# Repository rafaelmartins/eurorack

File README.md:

# eurorack

Designing and building an Eurorack synthesizer at home.

## General terms

- Everything other than the case and power supply should be designed from scratch, at home.
- PCBs are designed to be easily assembled at home.
- PTH is preferred, but SMD parts are allowed.
- Bare MCUs are preferred, but custom PCB-friendly development boards (like Raspberry Pi Pico) are allowed when the bare MCU is not easy to hand solder.

## License

Unless otherwise noted, these are the applicable licenses:

- Source code: [BSD 3-Clause "New" or "Revised" License](https://spdx.org/licenses/BSD-3-Clause.html)
- Hardware design (including 3d models, schematics, PCBs, etc): [CERN Open Hardware Licence Version 2 - Strongly Reciprocal](https://spdx.org/licenses/CERN-OHL-S-2.0.html)

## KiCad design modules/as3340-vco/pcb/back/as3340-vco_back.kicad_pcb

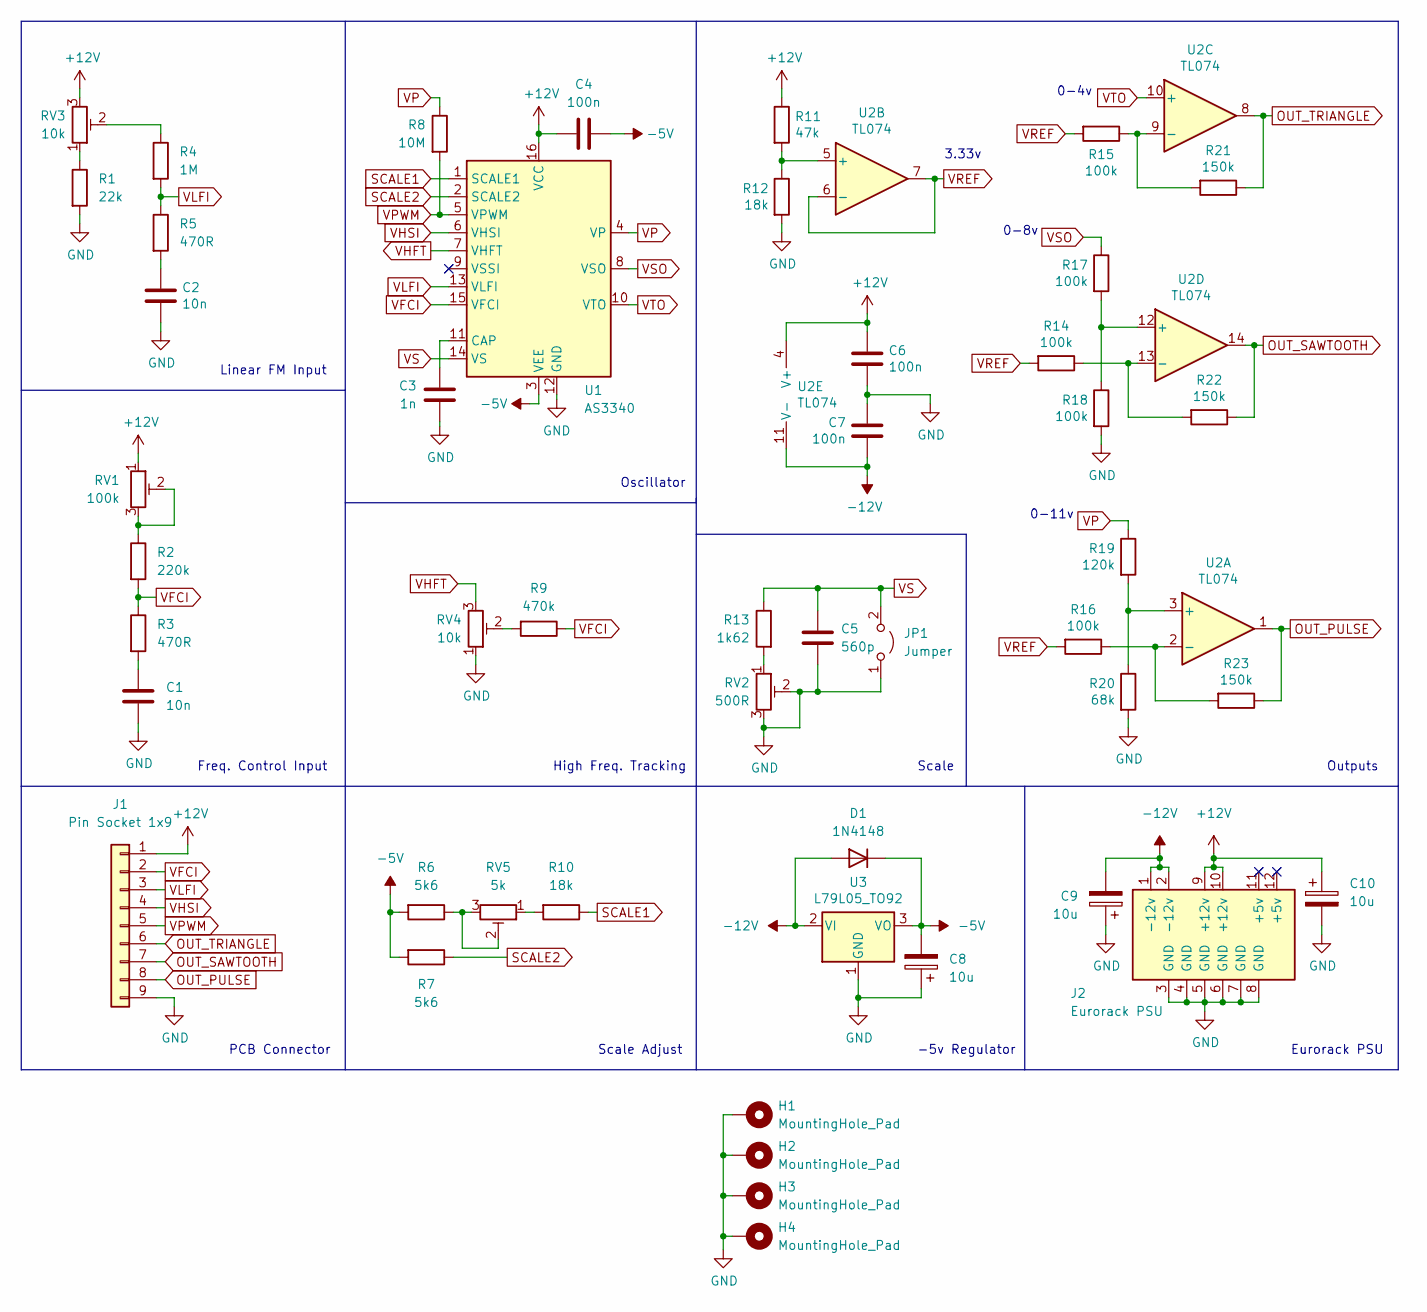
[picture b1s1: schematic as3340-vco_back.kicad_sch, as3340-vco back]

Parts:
C1, C2: 10n; C_Disc_D3.0mm_W1.6mm_P2.50mm
C3: 1n; C_Rect_L7.2mm_W3.0mm_P5.00mm_FKS2_FKP2_MKS2_MKP2
C4, C6, C7: 100n; C_Disc_D4.7mm_W2.5mm_P5.00mm
C5: 560p; C_Disc_D3.0mm_W1.6mm_P2.50mm
C8, C9, C10: 10u; CP_Radial_D5.0mm_P2.50mm
D1: 1N4148; D_DO-35_SOD27_P7.62mm_Horizontal
H1, H2, H3, H4: MountingHole_Pad; MountingHole_2.2mm_M2_Pad_Via
J1: Pin Socket 1x9; PinSocket_1x09_P2.54mm_Vertical
J2: Eurorack PSU; IDC-Header_2x08_P2.54mm_Vertical
JP1: Jumper; PinHeader_1x02_P2.54mm_Vertical
R1: 22k; R_Axial_DIN0207_L6.3mm_D2.5mm_P10.16mm_Horizontal
R2: 220k; R_Axial_DIN0207_L6.3mm_D2.5mm_P10.16mm_Horizontal
R3, R5: 470R; R_Axial_DIN0207_L6.3mm_D2.5mm_P10.16mm_Horizontal
R4: 1M; R_Axial_DIN0207_L6.3mm_D2.5mm_P10.16mm_Horizontal
R6, R7: 5k6; R_Axial_DIN0207_L6.3mm_D2.5mm_P10.16mm_Horizontal
R8: 10M; R_Axial_DIN0207_L6.3mm_D2.5mm_P10.16mm_Horizontal
R9: 470k; R_Axial_DIN0207_L6.3mm_D2.5mm_P10.16mm_Horizontal
R10, R12: 18k; R_Axial_DIN0207_L6.3mm_D2.5mm_P10.16mm_Horizontal
R11: 47k; R_Axial_DIN0207_L6.3mm_D2.5mm_P10.16mm_Horizontal
R13: 1k62; R_Axial_DIN0207_L6.3mm_D2.5mm_P10.16mm_Horizontal
R14, R15, R16, R17, R18: 100k; R_Axial_DIN0207_L6.3mm_D2.5mm_P10.16mm_Horizontal
R19: 120k; R_Axial_DIN0207_L6.3mm_D2.5mm_P10.16mm_Horizontal
R20: 68k; R_Axial_DIN0207_L6.3mm_D2.5mm_P10.16mm_Horizontal
R21, R22, R23: 150k; R_Axial_DIN0207_L6.3mm_D2.5mm_P10.16mm_Horizontal
RV1: 100k; Potentiometer_Vishay_M64Y_Horizontal
RV2: 500R; Potentiometer_Vishay_M64Y_Horizontal
RV3, RV4: 10k; Potentiometer_Vishay_M64Y_Horizontal
RV5: 5k; Potentiometer_Vishay_M64Y_Horizontal
U1: AS3340; DIP-16_W7.62mm
U2: TL074; DIP-14_W7.62mm
U3: L79L05_TO92; TO-92_Wide

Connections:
+12V: C4.1, C6.1, C10.1, J1.1, J2.9 (+12v), J2.10 (+12v), R11.1, RV1.1, RV3.3, U1.16 (VCC), U2.4 (V+)
-5V: C4.2, C8.2, D1.1 (K), R6.2, R7.2, U1.3 (VEE), U3.3 (VO)
-12V: C7.2, C9.2, D1.2 (A), J2.1 (-12v), J2.2 (-12v), U2.11 (V-), U3.2 (VI)
GND: C1.2, C2.2, C3.2, C5.2, C6.2, C7.1, C8.1, C9.1, C10.2, H1.1, H2.1, H3.1, H4.1, J1.9, J2.3 (GND), J2.4 (GND), J2.5 (GND), J2.6 (GND), J2.7 (GND), J2.8 (GND), JP1.1 (A), R1.2, R12.2, R18.2, R20.2, RV2.2, RV2.3, RV4.1, U1.12 (GND), U3.1 (GND)
unnamed: C1.1, R3.2
unnamed: C2.1, R5.2
unnamed: C3.1, U1.11 (CAP)
unnamed: R1.1, RV3.1
unnamed: R2.1, RV1.2, RV1.3
unnamed: R4.1, RV3.2
unnamed: R6.1, RV5.2, RV5.3
unnamed: R9.2, RV4.2
unnamed: R10.2, RV5.1
unnamed: R11.2, R12.1, U2.5 (+)
unnamed: R13.2, RV2.1
unnamed: R14.1, R22.2, U2.13 (-)
unnamed: R15.1, R21.2, U2.9 (-)
unnamed: R16.1, R23.2, U2.2 (-)
unnamed: R17.2, R18.1, U2.12 (+)
unnamed: R19.2, R20.1, U2.3 (+)
OUT_PULSE: J1.8, R23.1, U2.1
OUT_SAWTOOTH: J1.7, R22.1, U2.14
OUT_TRIANGLE: J1.6, R21.1, U2.8
SCALE1: R10.1, U1.1 (SCALE1)
SCALE2: R7.1, U1.2 (SCALE2)
VFCI: J1.2, R2.2, R3.1, R9.1, U1.15 (VFCI)
VHFT: RV4.3, U1.7 (VHFT)
VHSI: J1.4, U1.6 (VHSI)
VLFI: J1.3, R4.2, R5.1, U1.13 (VLFI)
VP: R8.1, R19.1, U1.4 (VP)
VPWM: J1.5, R8.2, U1.5 (VPWM)
VREF: R14.2, R15.2, R16.2, U2.6 (-), U2.7
VS: C5.1, JP1.2 (B), R13.1, U1.14 (VS)
VSO: R17.1, U1.8 (VSO)
VTO: U1.10 (VTO), U2.10 (+)

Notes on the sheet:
PCB Connector
Oscillator
-5v Regulator
Linear FM Input
Freq. Control Input
High Freq. Tracking
0-4v
Outputs
3.33v
0-8v
Eurorack PSU
Scale Adjust
0-11v
Scale

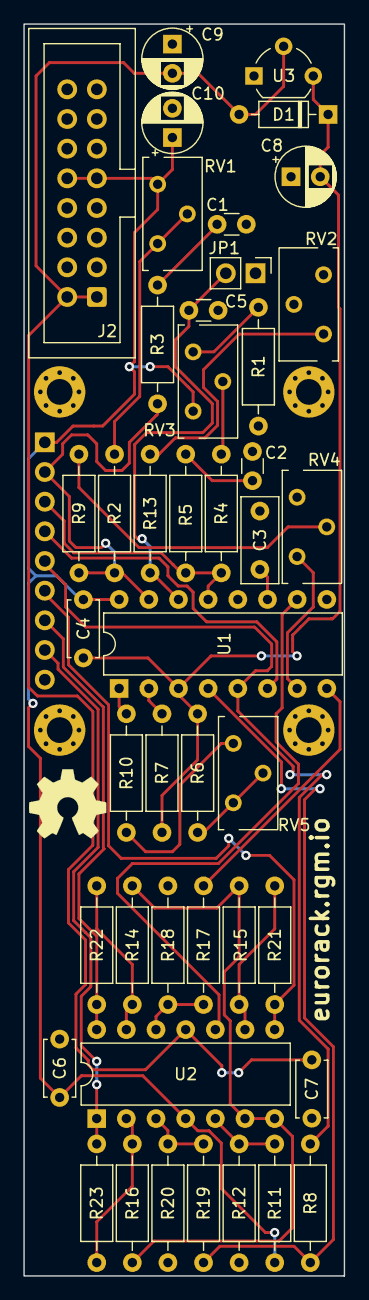
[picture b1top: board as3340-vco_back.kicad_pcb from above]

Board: 2 copper layers, 27.4 x 107.2 mm, 49 parts (1 on the bottom side), 35 nets.

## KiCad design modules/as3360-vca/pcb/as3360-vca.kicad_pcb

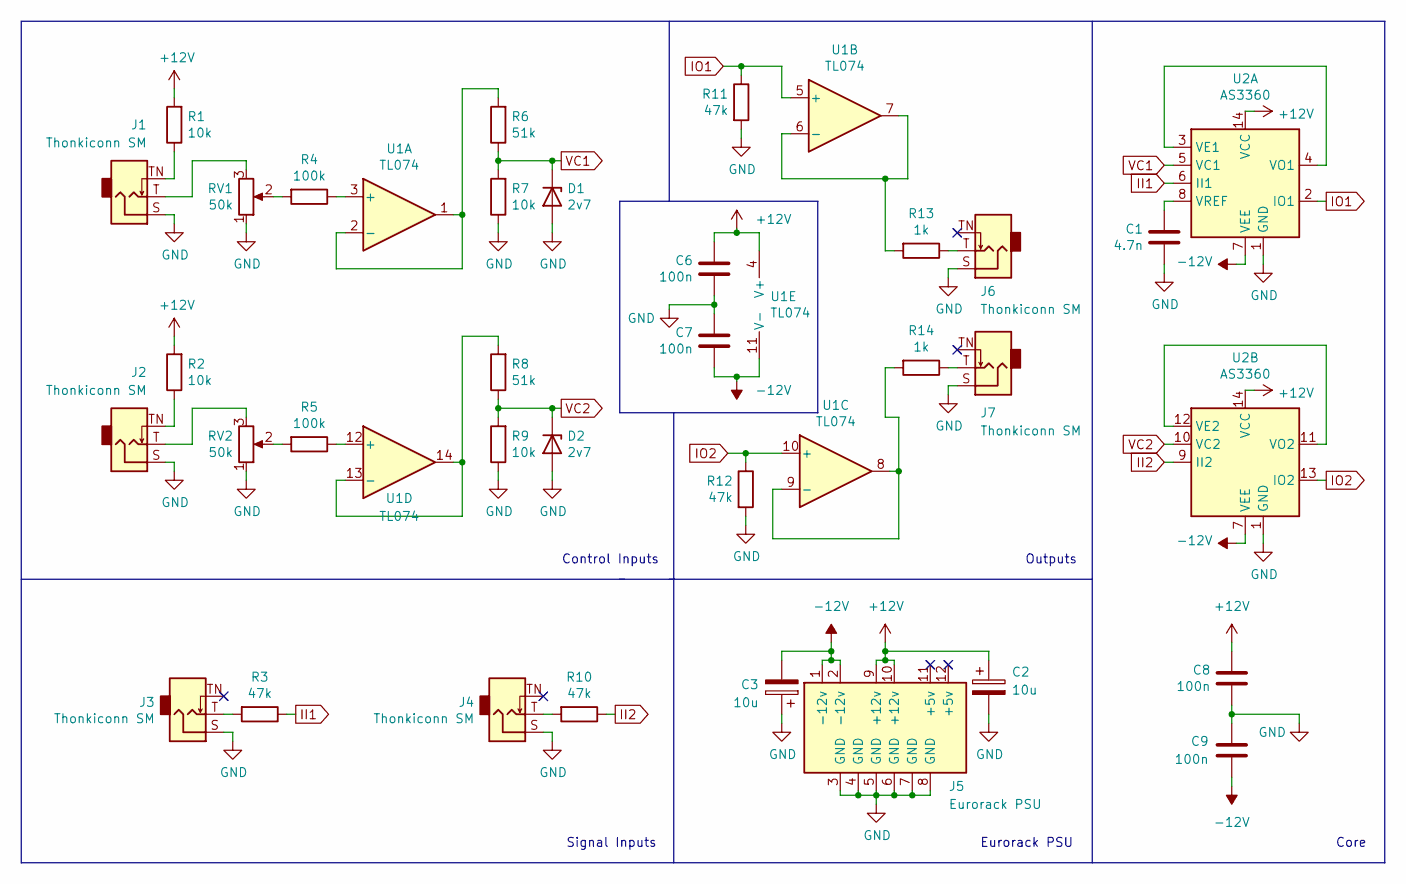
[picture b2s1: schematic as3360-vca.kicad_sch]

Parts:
C1: 4.7n; C_Rect_L7.0mm_W2.5mm_P5.00mm
C2, C3: 10u; CP_Radial_D5.0mm_P2.50mm
C6, C7, C8, C9: 100n; C_Disc_D4.3mm_W1.9mm_P5.00mm
D1, D2: 2v7; D_DO-35_SOD27_P7.62mm_Horizontal
J1, J2, J3, J4, J6, J7: Thonkiconn SM; Jack_3.5mm_QingPu_WQP-PJ398SM_Vertical
J5: Eurorack PSU; IDC-Header_2x08_P2.54mm_Vertical
R1, R2, R7, R9: 10k; R_Axial_DIN0207_L6.3mm_D2.5mm_P10.16mm_Horizontal
R3, R10, R11, R12: 47k; R_Axial_DIN0207_L6.3mm_D2.5mm_P10.16mm_Horizontal
R4, R5: 100k; R_Axial_DIN0207_L6.3mm_D2.5mm_P10.16mm_Horizontal
R6, R8: 51k; R_Axial_DIN0207_L6.3mm_D2.5mm_P10.16mm_Horizontal
R13, R14: 1k; R_Axial_DIN0207_L6.3mm_D2.5mm_P10.16mm_Horizontal
RV1, RV2: 50k; Potentiometer_Alpha_RD901F-40-00D_Single_Vertical_CircularH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
U1: TL074; DIP-14_W7.62mm
U2: AS3360; DIP-14_W7.62mm

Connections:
+12V: C2.1, C6.1, C8.1, J5.9 (+12v), J5.10 (+12v), R1.2, R2.2, U1.4 (V+), U2.14 (VCC)
-12V: C3.2, C7.2, C9.2, J5.1 (-12v), J5.2 (-12v), U1.11 (V-), U2.7 (VEE)
GND: C1.2, C2.2, C3.1, C6.2, C7.1, C8.2, C9.1, D1.2 (A), D2.2 (A), J1.S, J2.S, J3.S, J4.S, J5.3 (GND), J5.4 (GND), J5.5 (GND), J5.6 (GND), J5.7 (GND), J5.8 (GND), J6.S, J7.S, R7.1, R9.1, R11.2, R12.2, RV1.1, RV2.1, U2.1 (GND)
II1: R3.1, U2.6 (II1)
II2: R10.1, U2.9 (II2)
IO1: R11.1, U1.5 (+), U2.2 (IO1)
IO2: R12.1, U1.10 (+), U2.13 (IO2)
unnamed: C1.1, U2.8 (VREF)
unnamed: J1.T, RV1.3
unnamed: J1.TN, R1.1
unnamed: J2.T, RV2.3
unnamed: J2.TN, R2.1
unnamed: J3.T, R3.2
unnamed: J4.T, R10.2
unnamed: J6.T, R13.1
unnamed: J7.T, R14.1
unnamed: R4.1, U1.3 (+)
unnamed: R4.2, RV1.2
unnamed: R5.1, U1.12 (+)
unnamed: R5.2, RV2.2
unnamed: R6.2, U1.1, U1.2 (-)
unnamed: R8.2, U1.13 (-), U1.14
unnamed: R13.2, U1.6 (-), U1.7
unnamed: R14.2, U1.8, U1.9 (-)
unnamed: U2.3 (VE1), U2.4 (VO1)
unnamed: U2.11 (VO2), U2.12 (VE2)
VC1: D1.1 (K), R6.1, R7.2, U2.5 (VC1)
VC2: D2.1 (K), R8.1, R9.2, U2.10 (VC2)

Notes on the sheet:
Core
Signal Inputs
Outputs
Eurorack PSU
Control Inputs

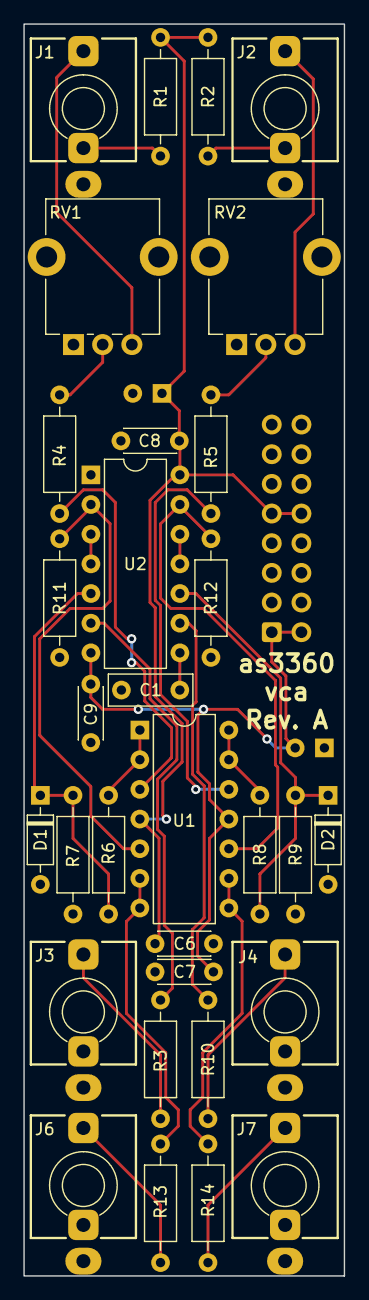
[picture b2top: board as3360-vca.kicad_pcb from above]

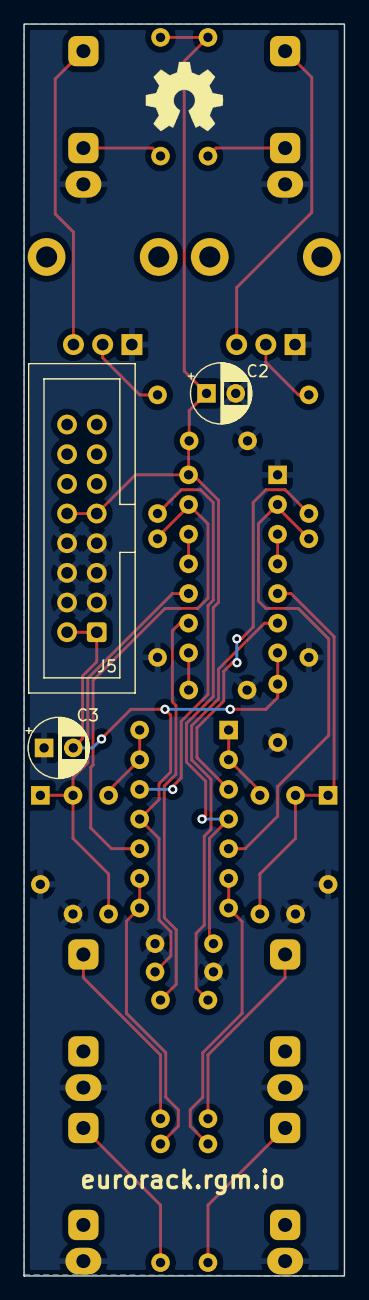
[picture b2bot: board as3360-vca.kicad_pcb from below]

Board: 2 copper layers, 27.4 x 107.2 mm, 34 parts (3 on the bottom side), 28 nets.

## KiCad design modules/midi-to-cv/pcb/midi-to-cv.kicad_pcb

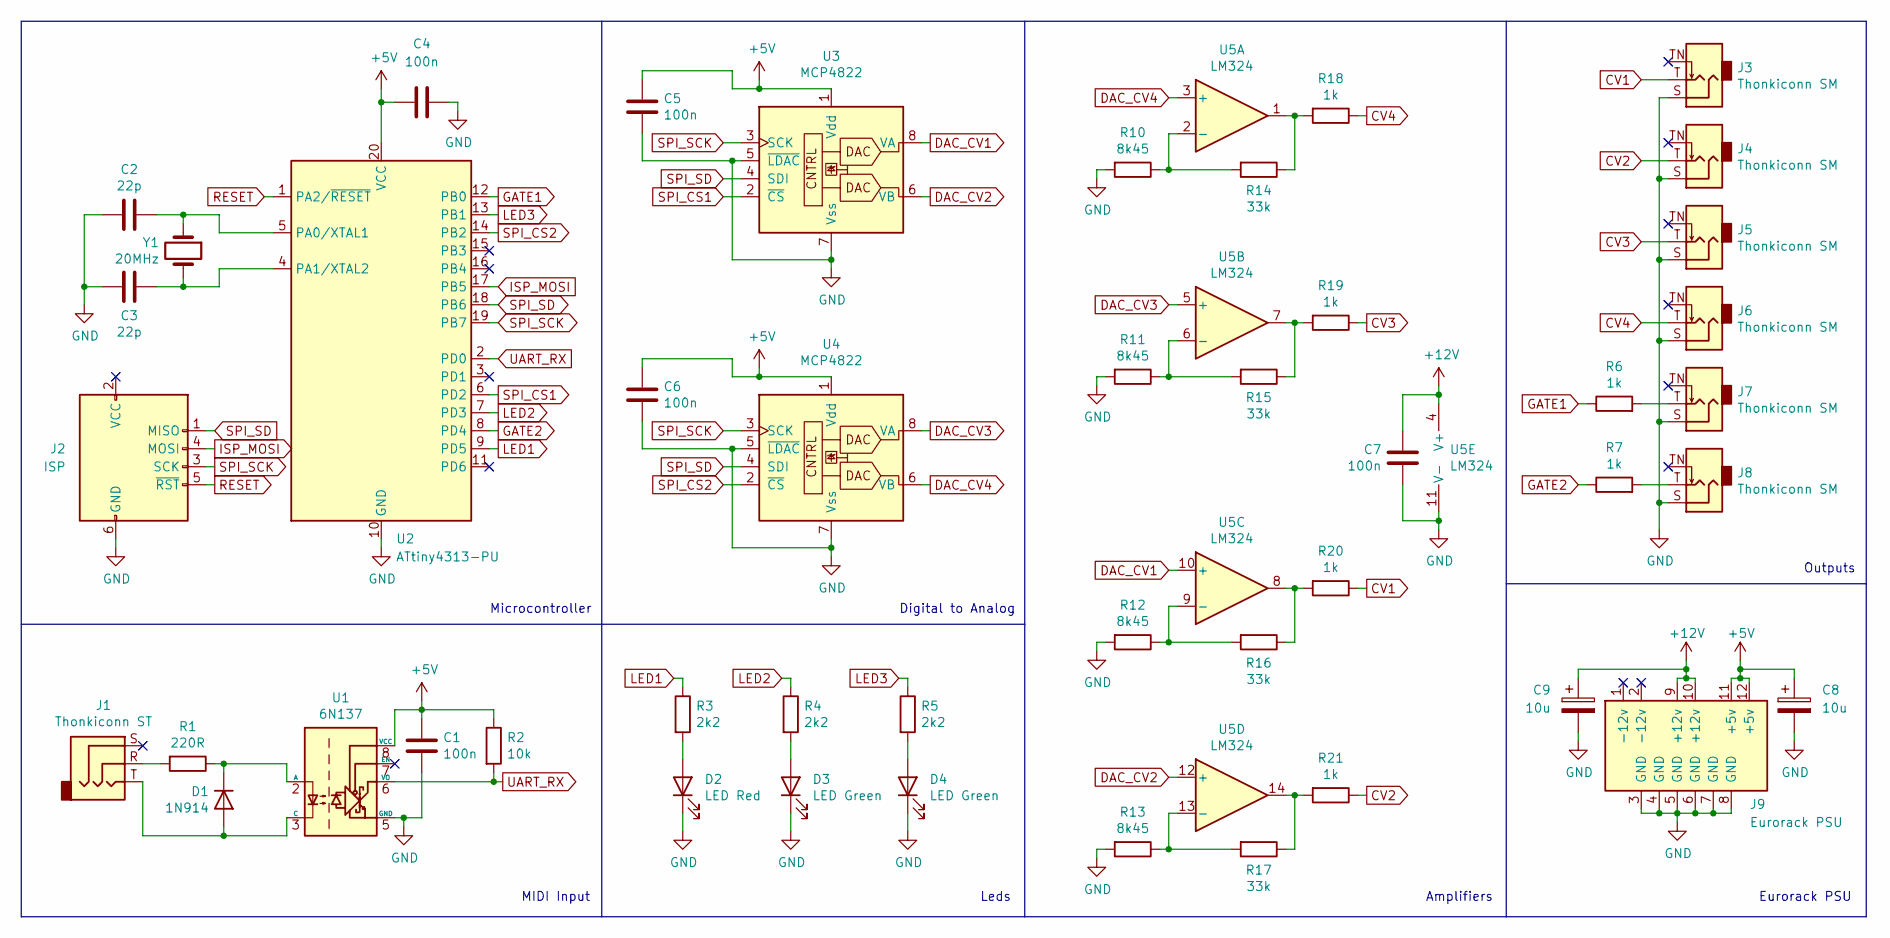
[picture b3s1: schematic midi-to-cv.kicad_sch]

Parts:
C1, C4, C5, C6, C7: 100n; C_Disc_D4.3mm_W1.9mm_P5.00mm
C2, C3: 22p; C_Disc_D3.0mm_W1.6mm_P2.50mm
C8, C9: 10u; CP_Radial_D5.0mm_P2.50mm
D1: 1N914; D_DO-35_SOD27_P7.62mm_Horizontal
D2: LED Red; LED_D3.0mm
D3, D4: LED Green; LED_D3.0mm
J1: Thonkiconn ST; Jack_3.5mm_QingPu_WQP-PJ366ST_Vertical
J2: ISP; IDC-Header_2x03_P2.54mm_Vertical
J3, J4, J5, J6, J7, J8: Thonkiconn SM; Jack_3.5mm_QingPu_WQP-PJ398SM_Vertical
J9: Eurorack PSU; IDC-Header_2x08_P2.54mm_Vertical
R1: 220R; R_Axial_DIN0207_L6.3mm_D2.5mm_P10.16mm_Horizontal
R2: 10k; R_Axial_DIN0207_L6.3mm_D2.5mm_P10.16mm_Horizontal
R3, R4, R5: 2k2; R_Axial_DIN0207_L6.3mm_D2.5mm_P10.16mm_Horizontal
R6, R7, R18, R19, R20, R21: 1k; R_Axial_DIN0207_L6.3mm_D2.5mm_P10.16mm_Horizontal
R10, R11, R12, R13: 8k45; R_Axial_DIN0207_L6.3mm_D2.5mm_P10.16mm_Horizontal
R14, R15, R16, R17: 33k; R_Axial_DIN0207_L6.3mm_D2.5mm_P10.16mm_Horizontal
U1: 6N137; DIP-8_W7.62mm
U2: ATtiny4313-PU; DIP-20_W7.62mm
U3, U4: MCP4822; DIP-8_W7.62mm
U5: LM324; DIP-14_W7.62mm
Y1: 20MHz; Crystal_HC49-U_Vertical

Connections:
+5V: C1.1, C4.1, C5.1, C6.1, C8.1, J9.11 (+5v), J9.12 (+5v), R2.1, U1.8 (VCC), U2.20 (VCC), U3.1 (Vdd), U4.1 (Vdd)
+12V: C7.1, C9.1, J9.9 (+12v), J9.10 (+12v), U5.4 (V+)
CV1: J3.T, R20.1
CV2: J4.T, R21.1
CV3: J5.T, R19.1
CV4: J6.T, R18.1
DAC_CV1: U3.8 (VA), U5.10 (+)
DAC_CV2: U3.6 (VB), U5.12 (+)
DAC_CV3: U4.8 (VA), U5.5 (+)
DAC_CV4: U4.6 (VB), U5.3 (+)
GATE1: R6.1, U2.12 (PB0)
GATE2: R7.1, U2.8 (PD4)
GND: C1.2, C2.2, C3.2, C4.2, C5.2, C6.2, C7.2, C8.2, C9.2, D2.1 (K), D3.1 (K), D4.1 (K), J2.6 (GND), J3.S, J4.S, J5.S, J6.S, J7.S, J8.S, J9.3 (GND), J9.4 (GND), J9.5 (GND), J9.6 (GND), J9.7 (GND), J9.8 (GND), R10.2, R11.2, R12.2, R13.2, U1.5 (GND), U2.10 (GND), U3.5 (~LDAC), U3.7 (Vss), U4.5 (~LDAC), U4.7 (Vss), U5.11 (V-)
ISP_MOSI: J2.4 (MOSI), U2.17 (PB5)
LED1: R3.1, U2.9 (PD5)
LED2: R4.1, U2.7 (PD3)
LED3: R5.1, U2.13 (PB1)
unnamed: C2.1, U2.5 (PA0/XTAL1), Y1.1
unnamed: C3.1, U2.4 (PA1/XTAL2), Y1.2
unnamed: D1.1 (K), R1.1, U1.2 (A)
unnamed: D1.2 (A), J1.T, U1.3 (C)
unnamed: D2.2 (A), R3.2
unnamed: D3.2 (A), R4.2
unnamed: D4.2 (A), R5.2
unnamed: J1.R, R1.2
unnamed: J7.T, R6.2
unnamed: J8.T, R7.2
unnamed: R10.1, R14.2, U5.2 (-)
unnamed: R11.1, R15.2, U5.6 (-)
unnamed: R12.1, R16.2, U5.9 (-)
unnamed: R13.1, R17.2, U5.13 (-)
unnamed: R14.1, R18.2, U5.1
unnamed: R15.1, R19.2, U5.7
unnamed: R16.1, R20.2, U5.8
unnamed: R17.1, R21.2, U5.14
RESET: J2.5 (~RST), U2.1 (PA2/~RESET)
SPI_CS1: U2.6 (PD2), U3.2 (~CS)
SPI_CS2: U2.14 (PB2), U4.2 (~CS)
SPI_SCK: J2.3 (SCK), U2.19 (PB7), U3.3 (SCK), U4.3 (SCK)
SPI_SD: J2.1 (MISO), U2.18 (PB6), U3.4 (SDI), U4.4 (SDI)
UART_RX: R2.2, U1.6 (VO), U2.2 (PD0)

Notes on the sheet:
Leds
Digital to Analog
Eurorack PSU
Outputs
Amplifiers
MIDI Input
Microcontroller

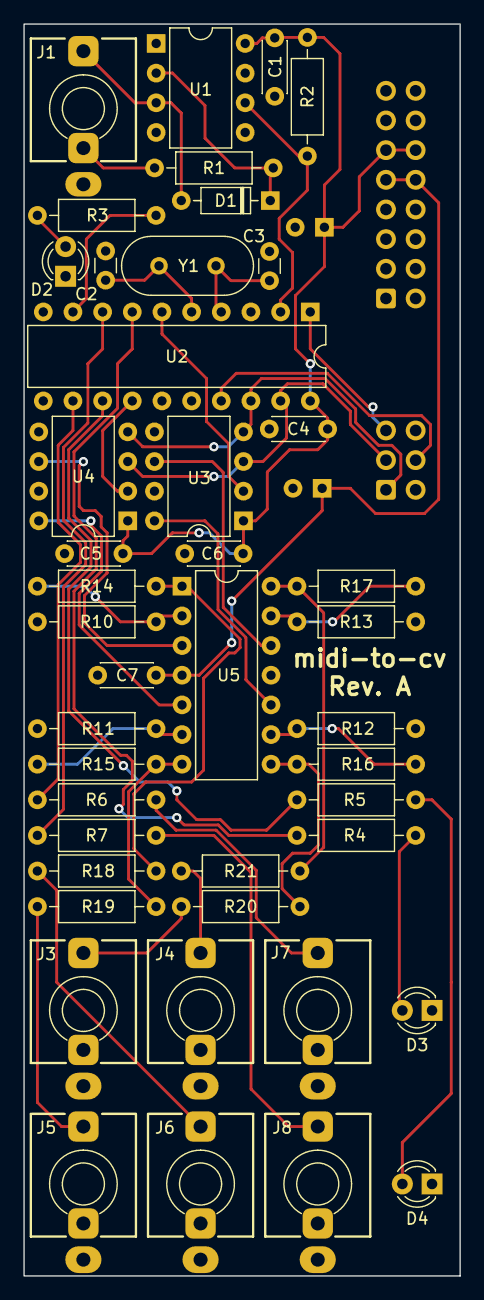
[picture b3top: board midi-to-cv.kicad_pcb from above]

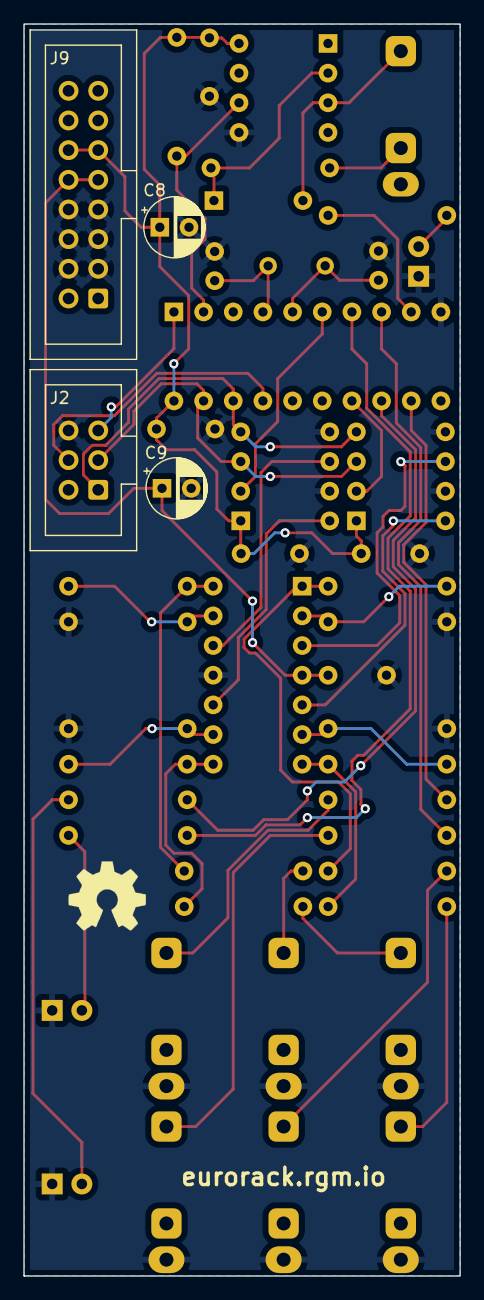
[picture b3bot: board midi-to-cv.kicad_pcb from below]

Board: 2 copper layers, 37.3 x 107.2 mm, 47 parts (4 on the bottom side), 41 nets.

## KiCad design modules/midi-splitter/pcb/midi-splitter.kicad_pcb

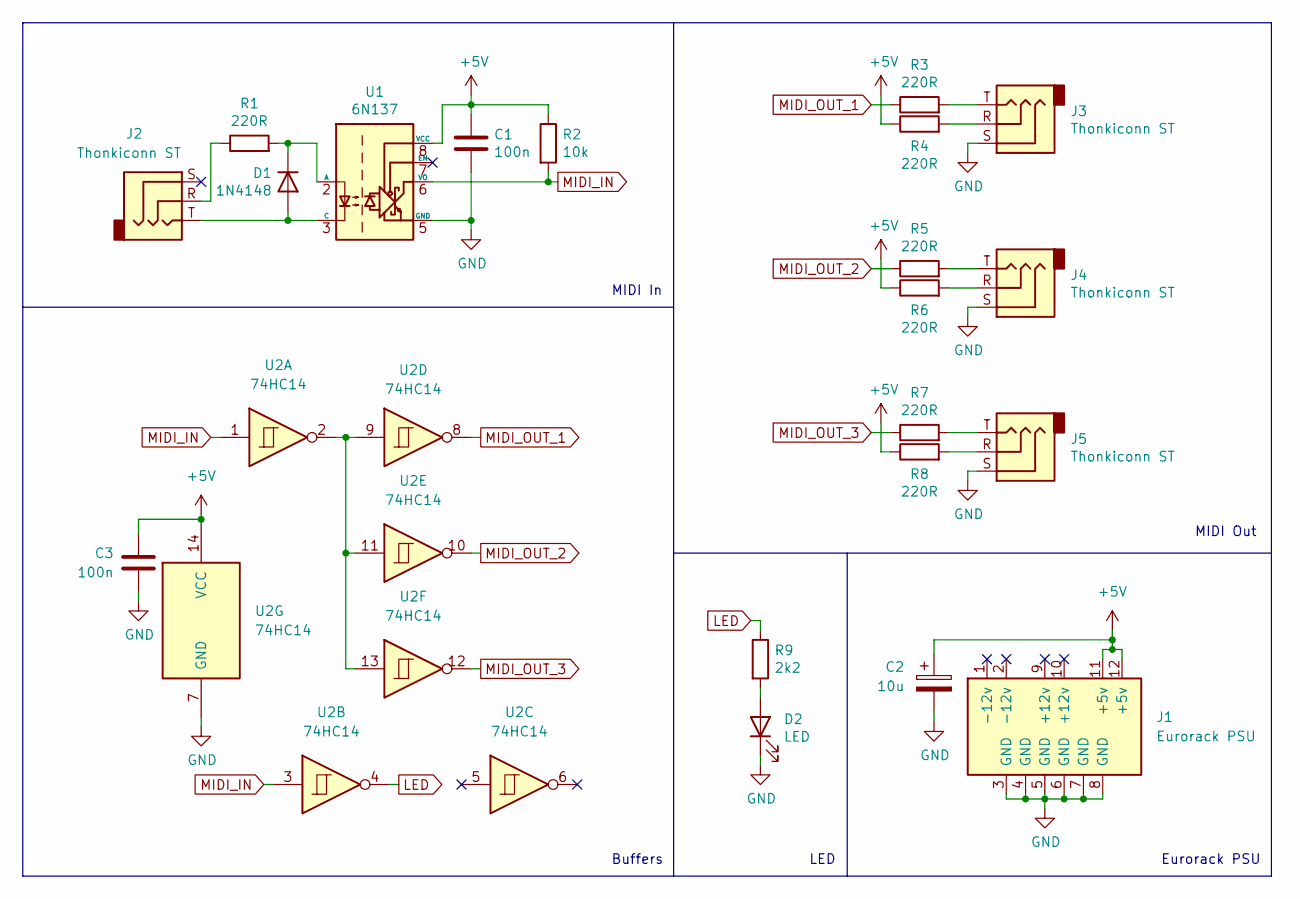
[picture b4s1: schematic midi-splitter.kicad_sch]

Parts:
C1, C3: 100n; C_Disc_D4.3mm_W1.9mm_P5.00mm
C2: 10u; CP_Radial_D5.0mm_P2.50mm
D1: 1N4148; D_DO-35_SOD27_P7.62mm_Horizontal
D2: LED; LED_D3.0mm
J1: Eurorack PSU; IDC-Header_2x08_P2.54mm_Vertical
J2, J3, J4, J5: Thonkiconn ST; Jack_3.5mm_QingPu_WQP-PJ366ST_Vertical
R1, R3, R4, R5, R6, R7, R8: 220R; R_Axial_DIN0207_L6.3mm_D2.5mm_P10.16mm_Horizontal
R2: 10k; R_Axial_DIN0207_L6.3mm_D2.5mm_P10.16mm_Horizontal
R9: 2k2; R_Axial_DIN0207_L6.3mm_D2.5mm_P10.16mm_Horizontal
U1: 6N137; DIP-8_W7.62mm
U2: 74HC14; DIP-14_W7.62mm

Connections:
+5V: C1.1, C2.1, C3.1, J1.11 (+5v), J1.12 (+5v), R2.1, R4.1, R6.1, R8.1, U1.8 (VCC), U2.14 (VCC)
GND: C1.2, C2.2, C3.2, D2.1 (K), J1.3 (GND), J1.4 (GND), J1.5 (GND), J1.6 (GND), J1.7 (GND), J1.8 (GND), J3.S, J4.S, J5.S, U1.5 (GND), U2.7 (GND)
LED: R9.1, U2.4
MIDI_IN: R2.2, U1.6 (VO), U2.1, U2.3
MIDI_OUT_1: R3.1, U2.8
MIDI_OUT_2: R5.1, U2.10
MIDI_OUT_3: R7.1, U2.12
unnamed: D1.1 (K), R1.2, U1.2 (A)
unnamed: D1.2 (A), J2.T, U1.3 (C)
unnamed: D2.2 (A), R9.2
unnamed: J2.R, R1.1
unnamed: J3.R, R4.2
unnamed: J3.T, R3.2
unnamed: J4.R, R6.2
unnamed: J4.T, R5.2
unnamed: J5.R, R8.2
unnamed: J5.T, R7.2
unnamed: U2.2, U2.9, U2.11, U2.13

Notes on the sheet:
LED
MIDI In
Buffers
Eurorack PSU
MIDI Out

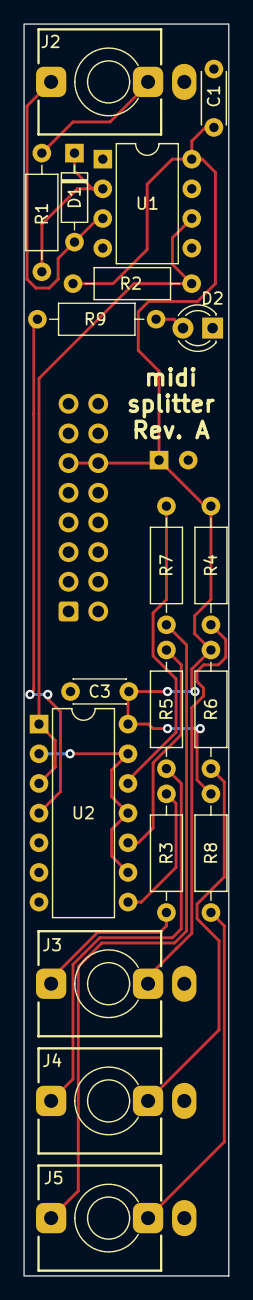
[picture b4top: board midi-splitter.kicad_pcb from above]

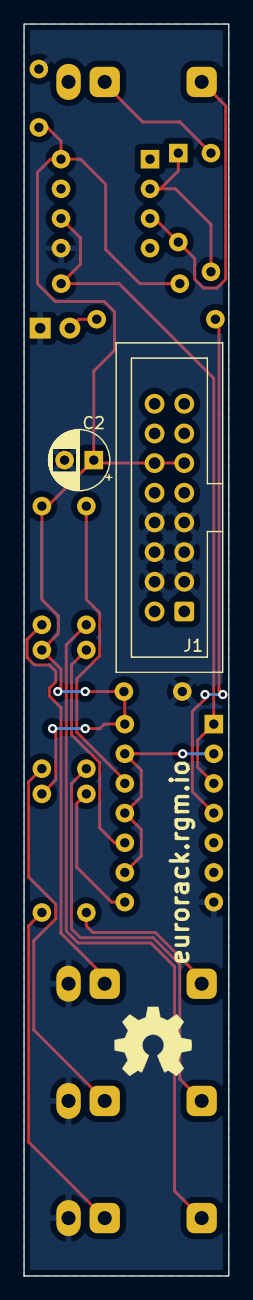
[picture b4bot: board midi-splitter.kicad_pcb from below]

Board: 2 copper layers, 17.5 x 107.2 mm, 21 parts (2 on the bottom side), 18 nets.

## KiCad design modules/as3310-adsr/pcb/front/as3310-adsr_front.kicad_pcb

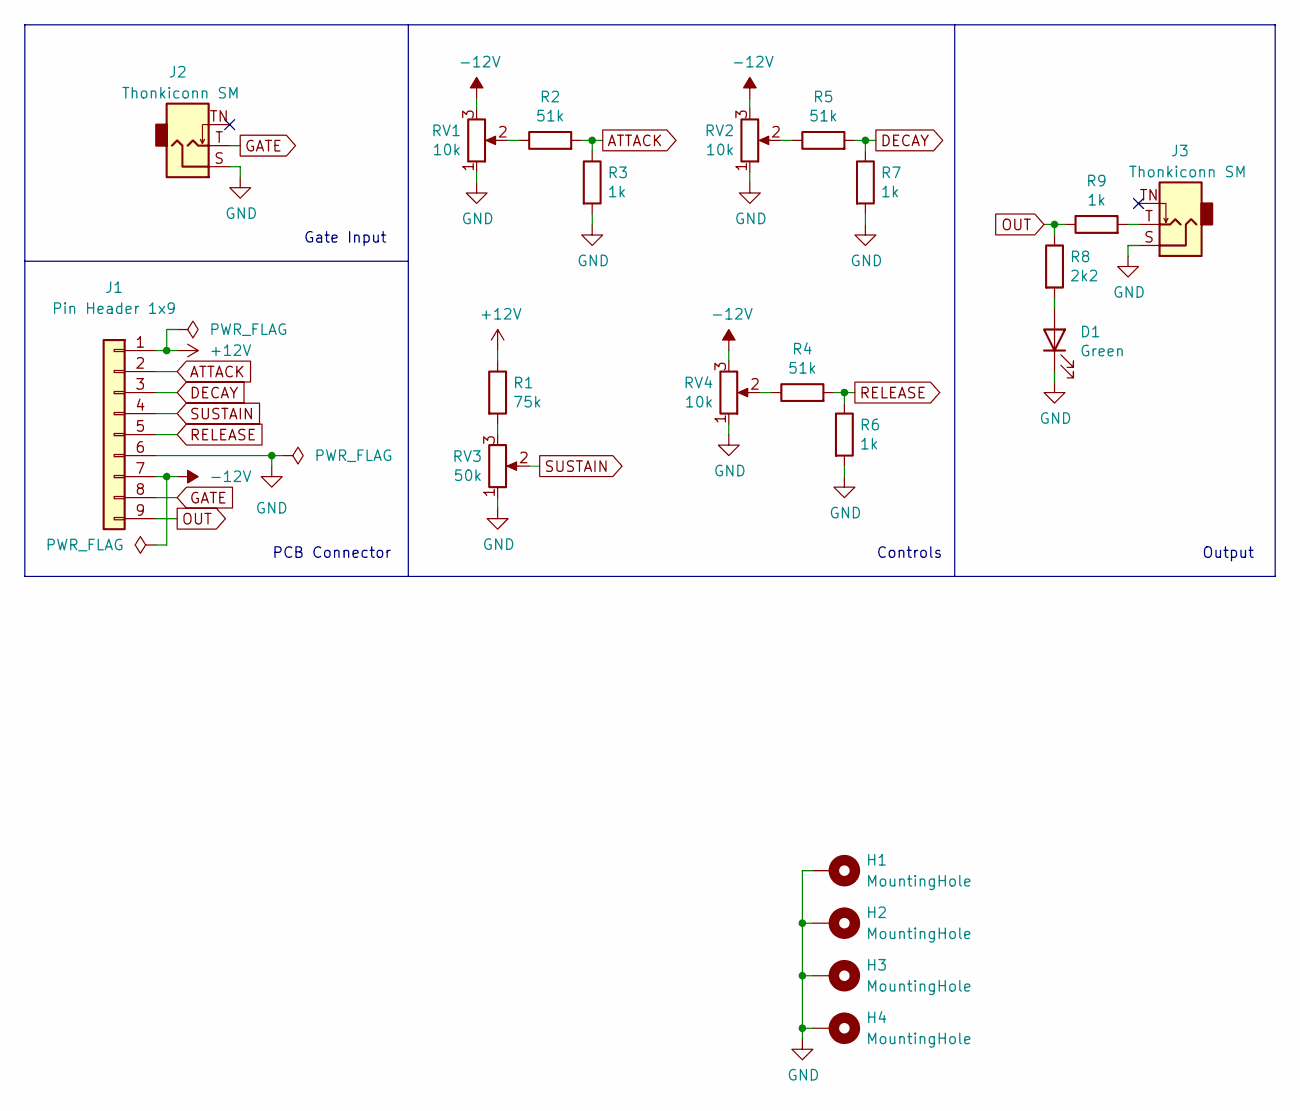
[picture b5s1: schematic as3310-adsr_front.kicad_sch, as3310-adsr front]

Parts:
D1: Green; LED_D3.0mm
H1, H2, H3, H4: MountingHole; MountingHole_2.2mm_M2_Pad_Via
J1: Pin Header 1x9; PinHeader_1x09_P2.54mm_Vertical
J2, J3: Thonkiconn SM; Jack_3.5mm_QingPu_WQP-PJ398SM_Vertical
R1: 75k; R_Axial_DIN0207_L6.3mm_D2.5mm_P10.16mm_Horizontal
R2, R4, R5: 51k; R_Axial_DIN0207_L6.3mm_D2.5mm_P10.16mm_Horizontal
R3, R6, R7, R9: 1k; R_Axial_DIN0207_L6.3mm_D2.5mm_P10.16mm_Horizontal
R8: 2k2; R_Axial_DIN0207_L6.3mm_D2.5mm_P10.16mm_Horizontal
RV1, RV2, RV4: 10k; Potentiometer_Alpha_RD901F-40-00D_Single_Vertical_CircularH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
RV3: 50k; Potentiometer_Alpha_RD901F-40-00D_Single_Vertical_CircularH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

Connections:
+12V: J1.1, R1.1
-12V: J1.7, RV1.3, RV2.3, RV4.3
ATTACK: J1.2, R2.2, R3.1
DECAY: J1.3, R5.2, R7.1
GATE: J1.8, J2.T
GND: D1.1 (K), H1.1, H2.1, H3.1, H4.1, J1.6, J2.S, J3.S, R3.2, R6.2, R7.2, RV1.1, RV2.1, RV3.1, RV4.1
unnamed: D1.2 (A), R8.2
unnamed: J3.T, R9.2
unnamed: R1.2, RV3.3
unnamed: R2.1, RV1.2
unnamed: R4.1, RV4.2
unnamed: R5.1, RV2.2
OUT: J1.9, R8.1, R9.1
RELEASE: J1.5, R4.2, R6.1
SUSTAIN: J1.4, RV3.2

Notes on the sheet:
Controls
Gate Input
PCB Connector
Output

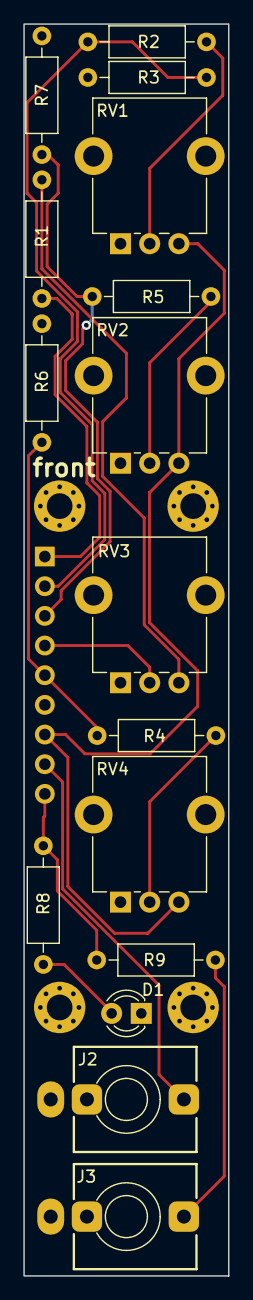
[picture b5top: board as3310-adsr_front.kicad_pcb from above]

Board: 2 copper layers, 17.5 x 107.2 mm, 21 parts (1 on the bottom side), 15 nets.

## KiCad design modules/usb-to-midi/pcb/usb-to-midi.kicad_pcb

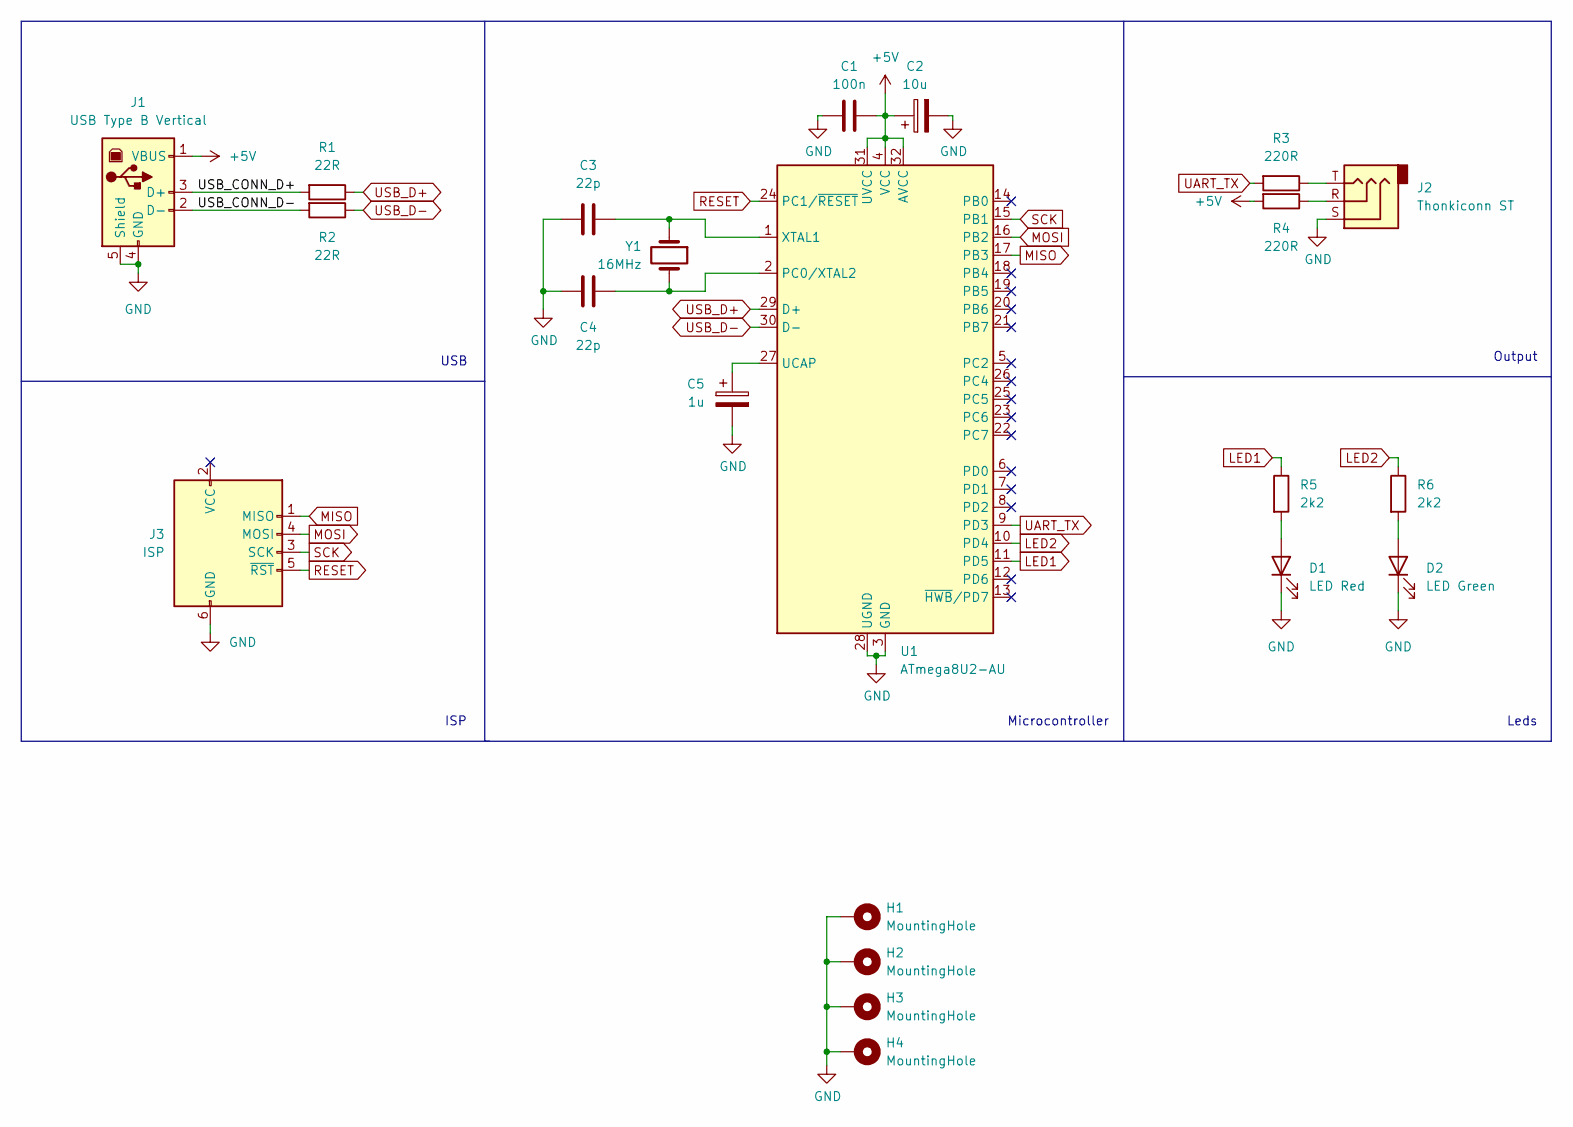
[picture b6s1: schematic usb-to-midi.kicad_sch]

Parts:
C1: 100n; C_Disc_D4.3mm_W1.9mm_P5.00mm
C2: 10u; CP_Radial_D5.0mm_P2.50mm
C3, C4: 22p; C_Disc_D3.0mm_W1.6mm_P2.50mm
C5: 1u; CP_Radial_D5.0mm_P2.50mm
D1: LED Red; LED_D3.0mm
D2: LED Green; LED_D3.0mm
H1, H2, H3, H4: MountingHole; MountingHole_2.2mm_M2_Pad_Via
J1: USB Type B Vertical; USB_B_TE_5787834_Vertical
J2: Thonkiconn ST; Jack_3.5mm_QingPu_WQP-PJ366ST_Vertical
J3: ISP; IDC-Header_2x03_P2.54mm_Vertical
R1, R2: 22R; R_Axial_DIN0207_L6.3mm_D2.5mm_P10.16mm_Horizontal
R3, R4: 220R; R_Axial_DIN0207_L6.3mm_D2.5mm_P10.16mm_Horizontal
R5, R6: 2k2; R_Axial_DIN0207_L6.3mm_D2.5mm_P10.16mm_Horizontal
U1: ATmega8U2-AU; TQFP-32_7x7mm_P0.8mm
Y1: 16MHz; Crystal_HC49-U_Vertical

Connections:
+5V: C1.2, C2.1, J1.1 (VBUS), R4.2, U1.4 (VCC), U1.31 (UVCC), U1.32 (AVCC)
/USB_CONN_D+: J1.3 (D+), R1.2
/USB_CONN_D-: J1.2 (D-), R2.2
GND: C1.1, C2.2, C3.2, C4.2, C5.2, D1.1 (K), D2.1 (K), H1.1, H2.1, H3.1, H4.1, J1.4 (GND), J1.5 (Shield), J2.S, J3.6 (GND), U1.3 (GND), U1.28 (UGND)
LED1: R5.1, U1.11 (PD5)
LED2: R6.1, U1.10 (PD4)
MISO: J3.1 (MISO), U1.17 (PB3)
MOSI: J3.4 (MOSI), U1.16 (PB2)
unnamed: C3.1, U1.1 (XTAL1), Y1.1
unnamed: C4.1, U1.2 (PC0/XTAL2), Y1.2
unnamed: C5.1, U1.27 (UCAP)
unnamed: D1.2 (A), R5.2
unnamed: D2.2 (A), R6.2
unnamed: J2.R, R4.1
unnamed: J2.T, R3.1
RESET: J3.5 (~RST), U1.24 (PC1/~RESET)
SCK: J3.3 (SCK), U1.15 (PB1)
UART_TX: R3.2, U1.9 (PD3)
USB_D+: R1.1, U1.29 (D+)
USB_D-: R2.1, U1.30 (D-)

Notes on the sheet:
Leds
USB
Microcontroller
ISP
Output

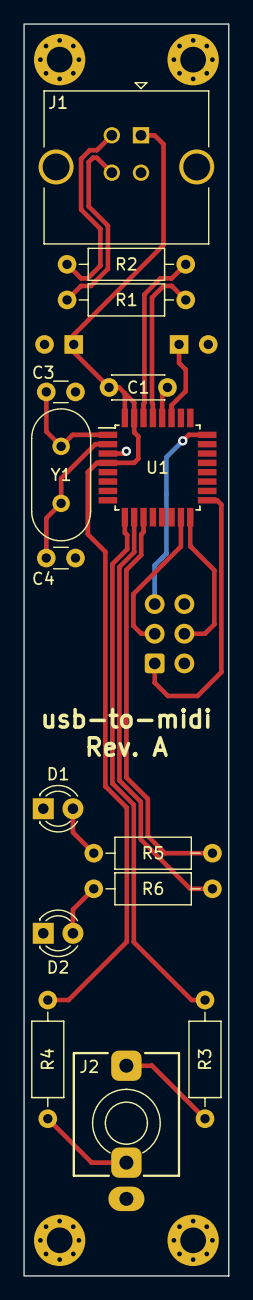
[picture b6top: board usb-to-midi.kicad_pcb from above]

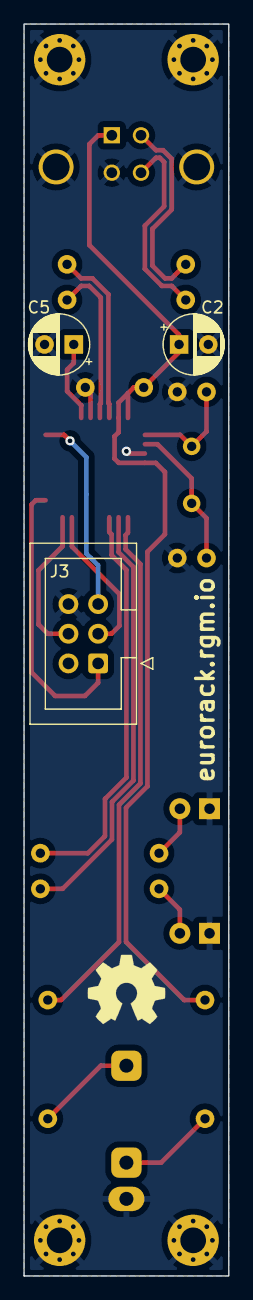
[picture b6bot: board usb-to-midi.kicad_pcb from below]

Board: 2 copper layers, 17.5 x 107.2 mm, 22 parts (3 on the bottom side), 20 nets.

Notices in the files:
modules/as3310-adsr/pcb/back/as3310-adsr_back.kicad_sch:
Released under CERN Open Hardware Licence Version 2 - Strongly Reciprocal
